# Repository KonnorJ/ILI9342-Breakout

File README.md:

# ILI9342-Breakout
Breakout for the ILI9342 51 pin 2.6 inch screen

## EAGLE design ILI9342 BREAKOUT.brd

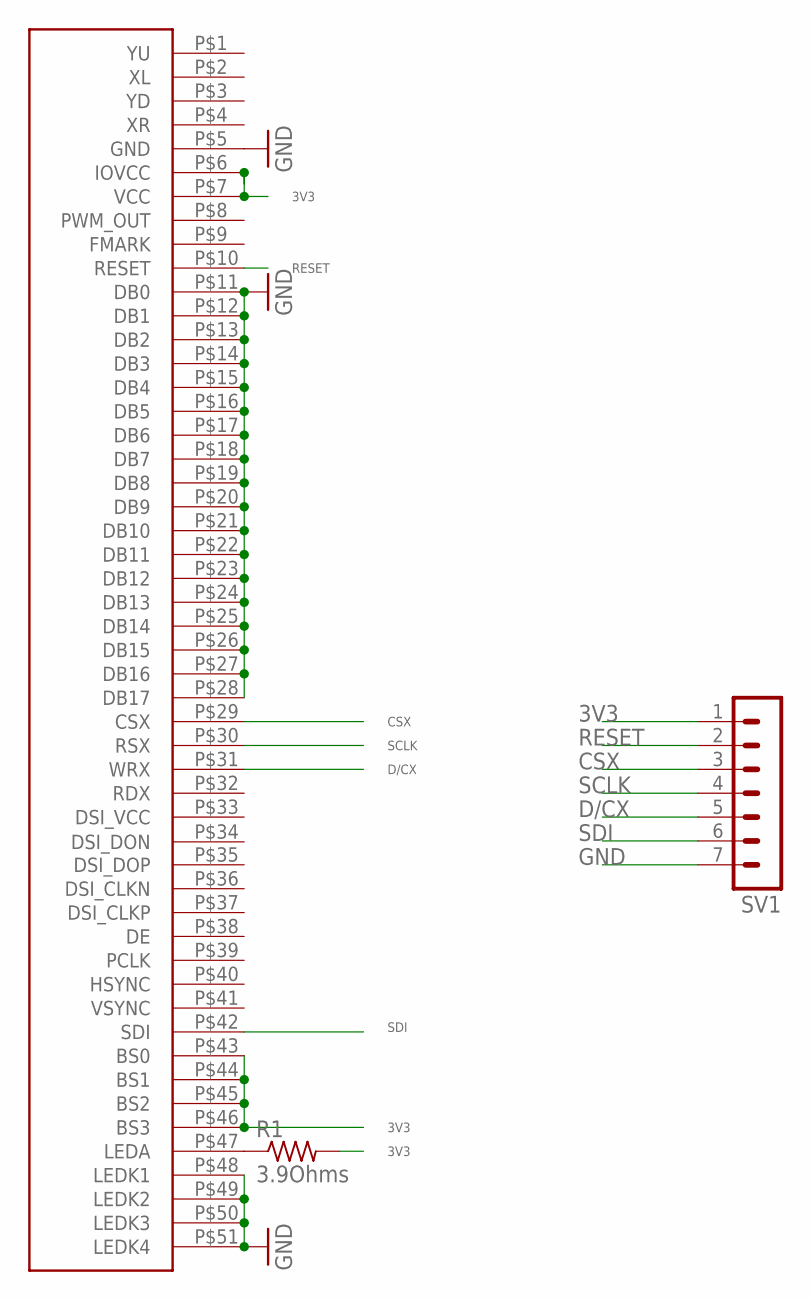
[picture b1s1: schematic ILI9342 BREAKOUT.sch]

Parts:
2.6ILI9342: TFT-DISPLAY-2.6-51PIN
R1: 3.9Ohms; R0805
SV1: MA07-1

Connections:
3V3: 2.6ILI9342.P$6 (IOVCC), 2.6ILI9342.P$7 (VCC), 2.6ILI9342.P$43 (BS0), 2.6ILI9342.P$44 (BS1), 2.6ILI9342.P$45 (BS2), 2.6ILI9342.P$46 (BS3), R1.2, SV1.1
CSX: 2.6ILI9342.P$29 (CSX), SV1.3
D/CX: 2.6ILI9342.P$31 (WRX), SV1.5
GND: 2.6ILI9342.P$5 (GND), 2.6ILI9342.P$11 (DB0), 2.6ILI9342.P$12 (DB1), 2.6ILI9342.P$13 (DB2), 2.6ILI9342.P$14 (DB3), 2.6ILI9342.P$15 (DB4), 2.6ILI9342.P$16 (DB5), 2.6ILI9342.P$17 (DB6), 2.6ILI9342.P$18 (DB7), 2.6ILI9342.P$19 (DB8), 2.6ILI9342.P$20 (DB9), 2.6ILI9342.P$21 (DB10), 2.6ILI9342.P$22 (DB11), 2.6ILI9342.P$23 (DB12), 2.6ILI9342.P$24 (DB13), 2.6ILI9342.P$25 (DB14), 2.6ILI9342.P$26 (DB15), 2.6ILI9342.P$27 (DB16), 2.6ILI9342.P$28 (DB17), 2.6ILI9342.P$48 (LEDK1), 2.6ILI9342.P$49 (LEDK2), 2.6ILI9342.P$50 (LEDK3), 2.6ILI9342.P$51 (LEDK4), SV1.7
unnamed: 2.6ILI9342.P$47 (LEDA), R1.1
RESET: 2.6ILI9342.P$10 (RESET), SV1.2
SCLK: 2.6ILI9342.P$30 (RSX), SV1.4
SDI: 2.6ILI9342.P$42 (SDI), SV1.6

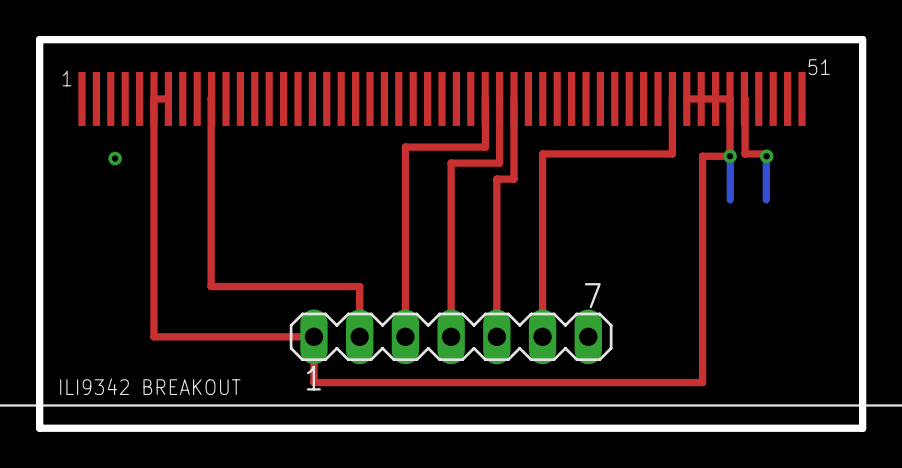
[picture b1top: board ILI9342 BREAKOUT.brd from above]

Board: 2 copper layers, 45.7 x 21.6 mm, 3 parts (1 on the bottom side), 8 nets.
